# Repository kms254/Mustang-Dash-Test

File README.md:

# Mustang-Dash-Test

Firmware **and carrier hardware** for a **Riverdi EVE4 instrument cluster** —
a 7" centre panel with two 5" side panels, each on its **own dedicated SPI
peripheral**, driven by an **STM32H755**.

| Item      | Value |
|-----------|-------|
| Displays  | Centre: Riverdi **SM-RVT70HSBNWN00** — 7.0" **1024 × 600** IPS, **BT817** (EVE4), no touch. Sides: RVT50H. |
| MCU       | **STM32H755ZIT6** on the in-repo carrier (**Board3**, ordered from JLCPCB 2026-08). Bench mules: NUCLEO-H755ZI-Q (same die) and NUCLEO-F767ZI (proven three-panel rig). |
| Library   | [RudolphRiedel/FT800-FT813](https://github.com/RudolphRiedel/FT800-FT813) (EmbeddedVideoEngine) v5.0.10, branch `5.x`, vendored in [`libraries/`](libraries/) with multi-panel / per-panel-SPI-bus support |
| Profile   | `EVE_RVT70H` (1024×600, BT817, `EVE_GEN 4`) |

## Repo layout

| Path | What it is |
|---|---|
| [`MustangDash/`](MustangDash/) | The firmware sketch plus pure, host-tested headers (sim, serial, odometer, button, telltales) |
| [`kicad/board3/`](kicad/board3/) | The carrier board — schematic, routed PCB, footprint libraries. DRC/ERC 0 at `--severity-all`; reviewed pre-order by seven independent lenses |
| [`fab/`](fab/) | The JLCPCB package: gerbers/BOM/CPL plus [`ORDER.md`](fab/ORDER.md), the order-form contract every figure of which re-derives from the tree |
| [`tools/`](tools/) | The KiCad pipeline: `kicad_lcsc.py` (sourcing), `kicad_fab.py` (fab package), `kicad_verify.py` (the DRC gate), silk/routing/verification tooling |
| [`docs/hardware/`](docs/hardware/) | [Bring-up card](docs/hardware/board3-bringup-card.md) (print before the boards arrive) and the [as-built H755 pin map](docs/hardware/board3-h755-pin-map.md) |
| [`docs/solutions/`](docs/solutions/) + [`CONCEPTS.md`](CONCEPTS.md) | Documented learnings (YAML frontmatter: `module`, `tags`, `problem_type`) and the shared domain vocabulary |

## Wiring

Shared ground, panel logic on **3.3 V**, backlight on an external **5.0 V**
supply (a dev board's USB rail cannot feed three backlights).

**Each panel has its own SPI peripheral** — on Board3: centre SPI1
(PA5/6/7, CS PD8, PD PD11), left SPI2 (PB13/14/15, CS PD9, PD PD12), right
SPI4 (PE2/5/6, CS PE3, PD PD13) — plus per-panel CS and PD/RST. Panel timings
live in [`MustangDash/dash_panels.h`](MustangDash/dash_panels.h); per-target
pins in the sketch's board blocks and the
[pin map](docs/hardware/board3-h755-pin-map.md). `INT` is not wired — the
firmware polls.

**SPI is mode 0, MSB-first, ≤ 11 MHz during every panel's `EVE_init()`**, then
each bus rises once to the run clock. **Board3 runs 25 MHz on all three
panels**, walked and soaked 2026-08-21; the F767 bench ran 13.5 (where 27 MHz
hard-wedges the firmware rather than degrading gracefully). Two numbers, two
clock trees, both correct — because clock numbers come from failure, not
derivation, and **do not transfer across copper**: re-walk on each new board,
per the bring-up card. And the constant is only a *request* — the peripheral
rounds it down to a reachable rung, so ask the firmware what it actually got
(`diag` on the serial console prints the attained rate per panel) rather than
trusting the source.

## What the firmware does

A 2000 ms animated boot splash (ASTC assets embedded in the MCU image and
staged to RAM_G with per-asset readback checks) crossfades into the dash, which
renders TRACK and STREET screens procedurally at ~60 fps with custom EVE bitmap
fonts.

Data flows simulator → `DashState` channels → renderers; CAN decoders will fill
the same channels later. The serial protocol (115200, USB-CDC on Board3;
`ok`/`err` acks) overrides any channel; the odometer persists across power
cycles. A short press on the gesture button (BTN1 on Board3, the USER button on
the mules) toggles TRACK/STREET; a ≥1 s hold resets the trip. Telltales drive
eight LEDs through two AW9523B expanders on I2C2; the boot banner self-checks
the panels, the expanders, and the QSPI NOR's JEDEC ID.

## Build

See [`BUILD.md`](BUILD.md) for the environments and the flash budget.

```bash
./scripts/compile.sh                    # PlatformIO, default env nucleo_f767
./scripts/compile.sh board3             # the carrier (25 MHz crystal clock tree)
./scripts/compile.sh board3_mule        # same firmware on the NUCLEO-H755ZI-Q
wsl -- bash -lc "./tests/run-tests.sh"  # host invariant tests, no board needed
```

**H755 targets, one-time first connect:** the factory chip boots both cores and
the CM4 has no image — run `STM32_Programmer_CLI -c port=SWD -ob BCM4=0` once.
The mule env is SMPS-aware (flashing plain `board3` onto the -Q Nucleo hangs at
the VOSRDY wait); details and the session matrix are on the
[bring-up card](docs/hardware/board3-bringup-card.md).

The host tests pin what must not silently change: the `EVE_RVT70H` profile, the
control pins, the backlight sweep, the splash timeline, the dash
math/sim/serial/odometer logic, the font format, the flash-pack layout, the
button gestures and the telltale calibration.

## Configuration (already applied in the vendored library)

- **Profile** — `EVE_config.h` defines `EVE_RVT70H` near the top of the file,
  so it applies without `-D` flags. Note it is **not** `EVE_RiTFT70`, which is
  the 800×480 BT81x panel — picking that one initialises fine and renders
  garbage. See [the profile-selection
  learning](docs/solutions/best-practices/riverdi-rvt70h-vs-ritft70-eve-display-profile-selection.md).
- **Multi-panel** — the STM32 target header carries `EVE_MULTI_PANEL` and a
  per-panel descriptor (`EVE_panel_t`) with an optional per-panel `SPIClass*`
  bus; the sketch selects the active panel at runtime.
- An Arduino `library.properties` was added so the `src/` layout is picked up
  (upstream ships only a PlatformIO `library.json`).

## Troubleshooting

| Symptom | Likely cause |
|---|---|
| Board looks completely dead | Hold **BOOT** + tap **RESET** → a DFU device on USB proves MCU, power and the USB path with zero tools. Then walk the [bring-up card](docs/hardware/board3-bringup-card.md); on this bench a "dead board" has historically been a cable or connector, not silicon. |
| `EVE_init() did NOT return E_OK` | EVE never came out of reset — check PD/RST, the 3.3 V logic supply, and CS. |
| Init OK but `REG_ID = 0x00`/`0xFF` (not `0x7C`) | SPI link — MISO/MOSI swapped, wrong CS, or the clock too fast. `0x00` and `0xFF` distinguish a floating line from a stuck one. |
| Init OK and `REG_ID = 0x7C` but the panel stays dark | Backlight power or `REG_PWM_DUTY`. The panel is alive but unlit — it renders fine with no 5 V on BLVDD, just invisibly. |
| Init OK, backlight lit, image garbled or wrong geometry | Wrong display profile in `EVE_config.h`. |

More hard-won detail — FFC orientation, identifying the backlight end by
continuity, why instruments that answer confidently deserve suspicion — is in
[`docs/solutions/`](docs/solutions/), organised by category with searchable
frontmatter.

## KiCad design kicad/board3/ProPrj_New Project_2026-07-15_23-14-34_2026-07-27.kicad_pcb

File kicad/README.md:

# kicad/

The project's board designs.

Today that is **Board3**. It arrived here as an import from EasyEDA Pro for the
tooling evaluation in
[docs/plans/2026-07-27-001-chore-kicad-evaluation-plan.md](../docs/plans/2026-07-27-001-chore-kicad-evaluation-plan.md),
but **that evaluation is settled**: as of 2026-07-31 Kevin has moved off EasyEDA
entirely, so this directory is the design, not a copy of one.

| Top | Bottom |
| --- | --- |
|  |  |

These are generated, not drawn — `.kicad_pcb` is the truth. See
[Renders](#renders) for how they stay current.

Three rules govern everything in this directory:

- **This is the source of truth.** ~~EasyEDA stays authoritative; conversion is
  one-way.~~ Superseded 2026-07-31 — EasyEDA is no longer maintained, so there is
  no upstream to defer to and nothing to reconcile against. Edit the schematic and
  board here directly. The `EasyEDA/` directory stays in the repo as history; do
  not mirror changes into it, and do not treat a KiCad-only change as partial.
  The one-way rule still describes the *import*: nothing here was ever converted
  back, and `docs/solutions/integration-issues/easyeda-pro-to-kicad-migration-silent-data-loss.md`
  records six silent losses that make a re-import a bad idea now that this copy
  carries all the routing.
- **The design files are tracked on purpose.** `.kicad_pcb` and `.kicad_sch` are
  S-expression text, and `git diff` is the evaluation's verification mechanism for
  agent-driven writes. Keeping the board out of the repo would forfeit that.
- **The first commit of a converted board is the baseline.** It must contain
  converter output and nothing else. Every later measurement diffs against it.

Toolchain resolution for anything operating on these files is
[tools/kicad_env.py](../tools/kicad_env.py) — do not hardcode `kicad-cli` paths.

**Never pick a board by globbing for the newest `.kicad_pcb`.** Routing and
cascade experiments leave variant boards (`…-c0.kicad_pcb`, `…-it.kicad_pcb`)
sitting beside the real one, and being scratch they are *always* newer — so
newest-wins reliably selects the wrong file. This bit twice on 2026-07-28:
`kicad_render.py` rendered a leftover temp board, and `kicad_live_view.py` spent
a session watching one that was then deleted underneath it. Filter to files git
tracks (`git ls-files -- '*.kicad_pcb'`) and take the newest of those; untracked
neighbours are working scratch, not the design.

## Renders

`board3/renders/*.png` are committed so the board is visible in a diff, a PR, or
a browser without installing KiCad. They are **build output, not source** — the
board is the truth and these are regenerated from it:

```sh
python tools/kicad_render.py            # refresh all three views
python tools/kicad_render.py --check    # exit 2 if older than the board
```

A tracked pre-commit hook keeps them honest. Install it once per clone:

```sh
git config core.hooksPath .githooks
```

The hook is convenience, not enforcement — it is opt-in per clone, so it is
silently absent on a fresh clone or under `--no-verify`. CI is what actually
holds the line: `.github/workflows/kicad-renders.yml` fails any PR that changes
the board without refreshing the renders, and `kicad-parts.yml` runs the part
audit on every PR.

The hook only fires when a `.kicad_pcb` is actually staged — each refresh is
~360 KB of binary that lands in history permanently, so regenerating on every
commit would bloat the repo to show a picture that did not change. If rendering
fails (no KiCad on this machine) it warns and lets the commit through: refusing
to commit firmware because a PCB picture could not be drawn is the wrong trade.

Renders are 1200×750 on purpose. Enough to read placement and routing at a
glance; open the board if you need detail.

## Watching the board change live

To see the board *while* an agent edits it, without pcbnew in the way:

```sh
python tools/kicad_live_view.py                     # newest board under kicad/
python tools/kicad_live_view.py path/to/x.kicad_pcb --port 8010
```

It serves a local page that renders the file with
[KiCanvas](https://kicanvas.org/) and reloads on every save, keeping your zoom.
Pan/zoom, layer toggles and net highlight all work.

**3D is on the second tab**, built by `kicad-cli` in the background — but only
while that tab is open, since a build costs real CPU and nobody would see it.
Two modes, because the cost difference is an order of magnitude:

| mode | what it is | board3 |
|---|---|---|
| **snapshot** (default) | `pcb render` PNG, six camera presets | **~3 s**, 0.1 MB |
| **model** | `export glb`, orbit in the browser | **~29 s**, 13.5 MB |
| **model + copper** | as above with tracks/zones/silk as geometry | **~47 s**, 31 MB |

So 3D follows an agent at roughly one frame per edit, not live — the header
always says how far behind it is (`3D showing rev 4, board at rev 7`) rather
than quietly showing you a stale board. Snapshot is the default because 3 s is
fast enough to actually watch work happen; switch to model when you want to
orbit something. There is no cheap middle: a components-free GLB builds in 1.2 s
but is a bare board, which is no use for checking a footprint.

Model mode opens **top-down on the top face** (model-viewer's own default is
nearly edge-on, which on a board this thin is a sliver). That framing is applied
once, so an orbit you set up afterwards survives every rebuild.

3D is built from the *same validated bytes* the 2D tab is showing, written to a
temp copy — so the two tabs can never disagree and a build can never catch a
half-written save. That relocation would normally drop every 3D model, since
footprints reference `${KIPRJMOD}/EASYEDA_MODELS/…` and KIPRJMOD follows the
file; the builder passes `-D KIPRJMOD=<board dir>` to put them back. Worth
knowing because the failure is silent — without it you get a bare green board
and no error.

**Why not just open pcbnew.** The editor takes a `.lck` on the board and holds
its own in-memory copy, so an agent's write and your session become two
authorities on one file — whoever saves last wins, silently. This viewer only
ever reads. That is also why it is a *viewer*: it is safe to leave open all day
precisely because it cannot write, so it does not replace the GUI for editing,
and KTD12 still holds (Update PCB from Schematic is Kevin, in the GUI, after a
restart).

Two things worth knowing:

- **A save is not atomic from the reader's side.** Every re-read is validated
  (starts with `(kicad_pcb`, parens balance outside strings) before it is
  published, so a file caught mid-write never reaches the screen — the viewer
  holds the last good revision and turns its status dot amber. Verified by
  truncating a board under a running viewer: revision held, bytes served
  unchanged.
- **KiCanvas predates KiCad 10 and skips tokens it does not know**, warning to
  the browser console. On board3 that is 344 warnings and zero errors, all of
  them non-geometry policy fields (`tenting`, `covering`, `plugging`, `capping`,
  `filling`, `duplicate_pad_numbers_are_jumpers`, dimension `units`). Copper,
  zones, footprints and silk all render. It is a preview, not an authority —
  DRC and the fab package remain the check that matters.

The bundle is cached to `tools/vendor/kicanvas.js` on first run (gitignored);
`--refresh-viewer` re-fetches it.

## Adding a part

**Every part placed on a board here must be an LCSC part, carrying supplier
metadata and a 3D model.** Not a convention — a build dependency. `kicad_fab.py`
builds the JLCPCB BOM by reading the schematic's supplier fields, so a part added
without them does not produce a warning, it produces a BOM that is quietly
missing a component.

Add parts with [tools/kicad_lcsc.py](../tools/kicad_lcsc.py), never by dragging a
generic symbol out of the stock KiCad libraries:

```sh
python tools/kicad_lcsc.py add C116592   # symbol + footprint + STEP/WRL + metadata
python tools/kicad_lcsc.py check         # audit; exits non-zero on any gap
python tools/kicad_lcsc.py models        # fetch any 3D model the board references but lacks
```

`add` drives the JLCImport plugin and then rewrites the imported symbol's fields
into Board3's vocabulary. That rewrite is the whole point: JLCImport writes the
LCSC code to a property named `LCSC`, and this project reads it from
`Supplier Part`. Import without remapping and the part looks sourced in the
schematic editor while being invisible to the BOM.

`LCSC Part Name` is **not** the part number despite its name — it holds
descriptive text. The C-number goes in `Supplier Part`.

Run `check` before generating fab output. It audits the **board**, not the
library — the board is what gets fabricated, and each placed footprint carries
its own copy of the model reference, so an instance placed before a library fix
can be wrong while the library looks perfect. It fails on any of:

- a placed part **not mapped to LCSC** (missing `Supplier Part`, or absent from
  the schematic entirely)
- a placed footprint with **no 3D model reference at all**
- a model reference whose **file is missing from disk**
- a schematic symbol with no LCSC code, placed or not

Footprints that legitimately have no body — fiducials, free pads, mounting
holes, test points — are exempt via the `BODILESS` table in the tool, and every
exemption is **printed on every run**. An exemption you cannot see is one you
cannot audit, and that table is the only path by which a real part could pass
unnoticed. Board3 currently exempts 8: three fiducials, four free pads (MP1-MP4) and H2, the Tag-Connect land pattern -- a cable presses pogo pins onto bare copper, so nothing is fitted and there is no part to source.

3D models live in `board3/EASYEDA_MODELS/` and **are tracked** (~53 MB, ~9.5 MB
in history). They are regenerable from the schematic's LCSC codes via
`kicad_lcsc.py models`, but they are committed anyway so a fresh clone renders
and exports 3D offline, and so the geometry stays pinned to this board revision
rather than to whatever EasyEDA serves later.

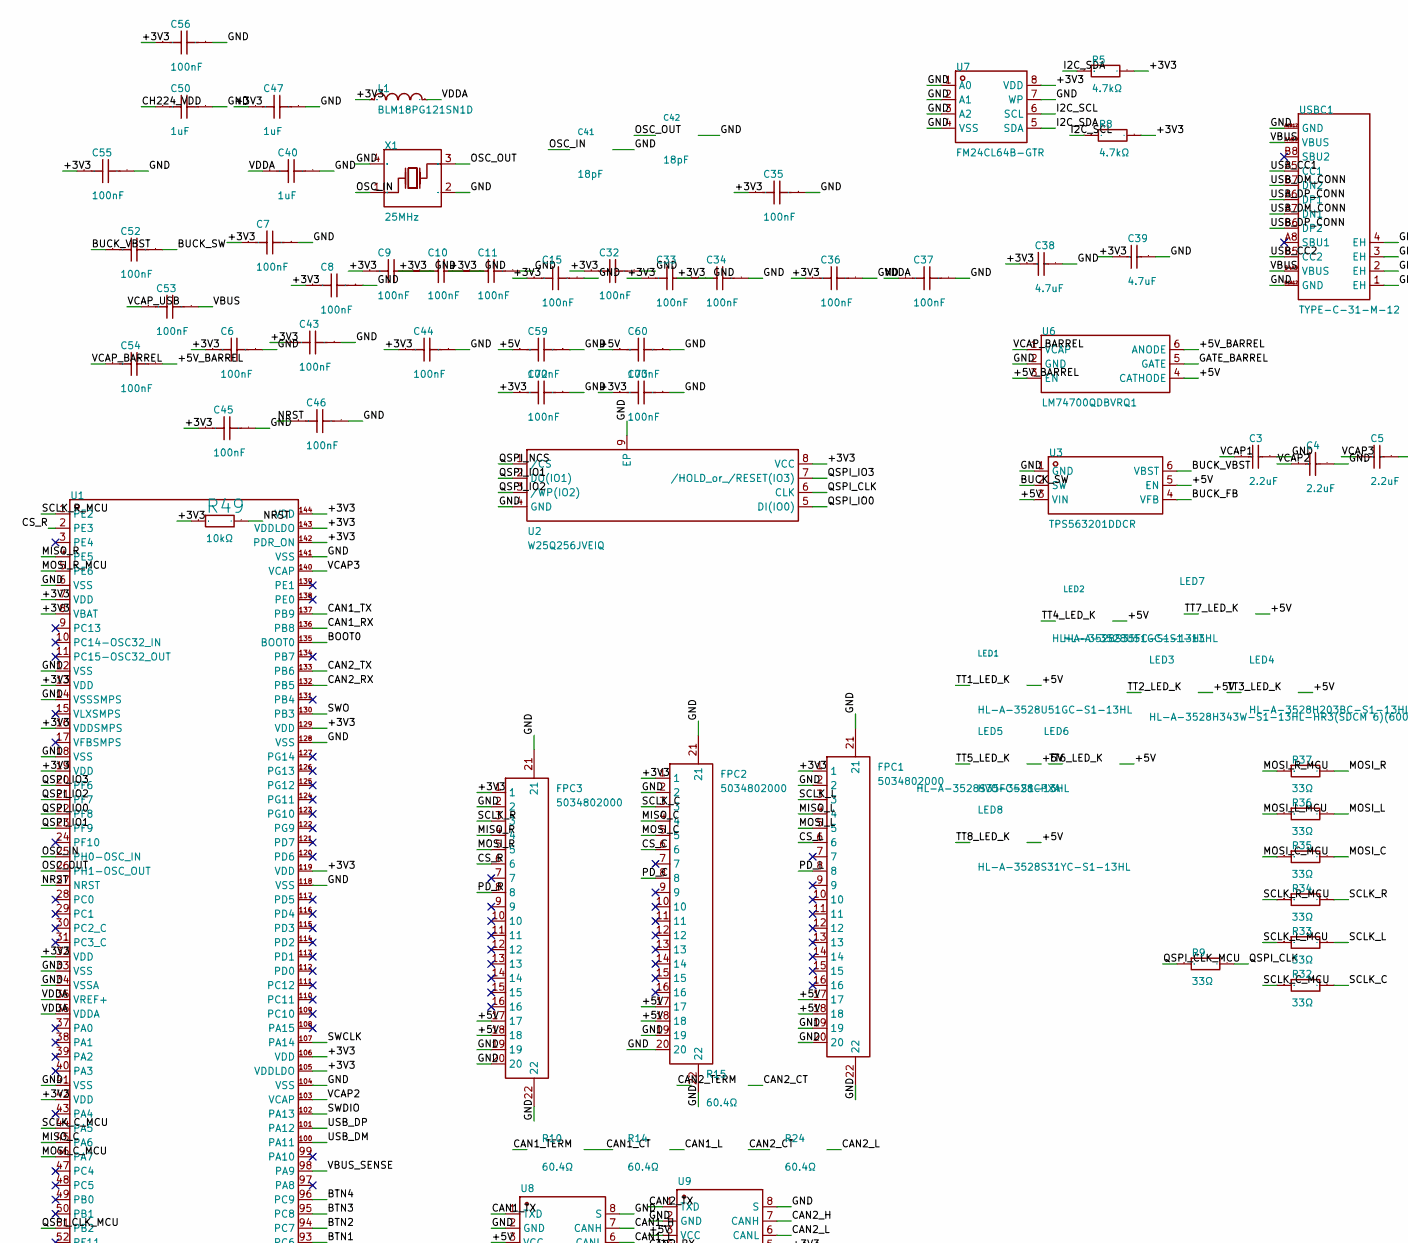
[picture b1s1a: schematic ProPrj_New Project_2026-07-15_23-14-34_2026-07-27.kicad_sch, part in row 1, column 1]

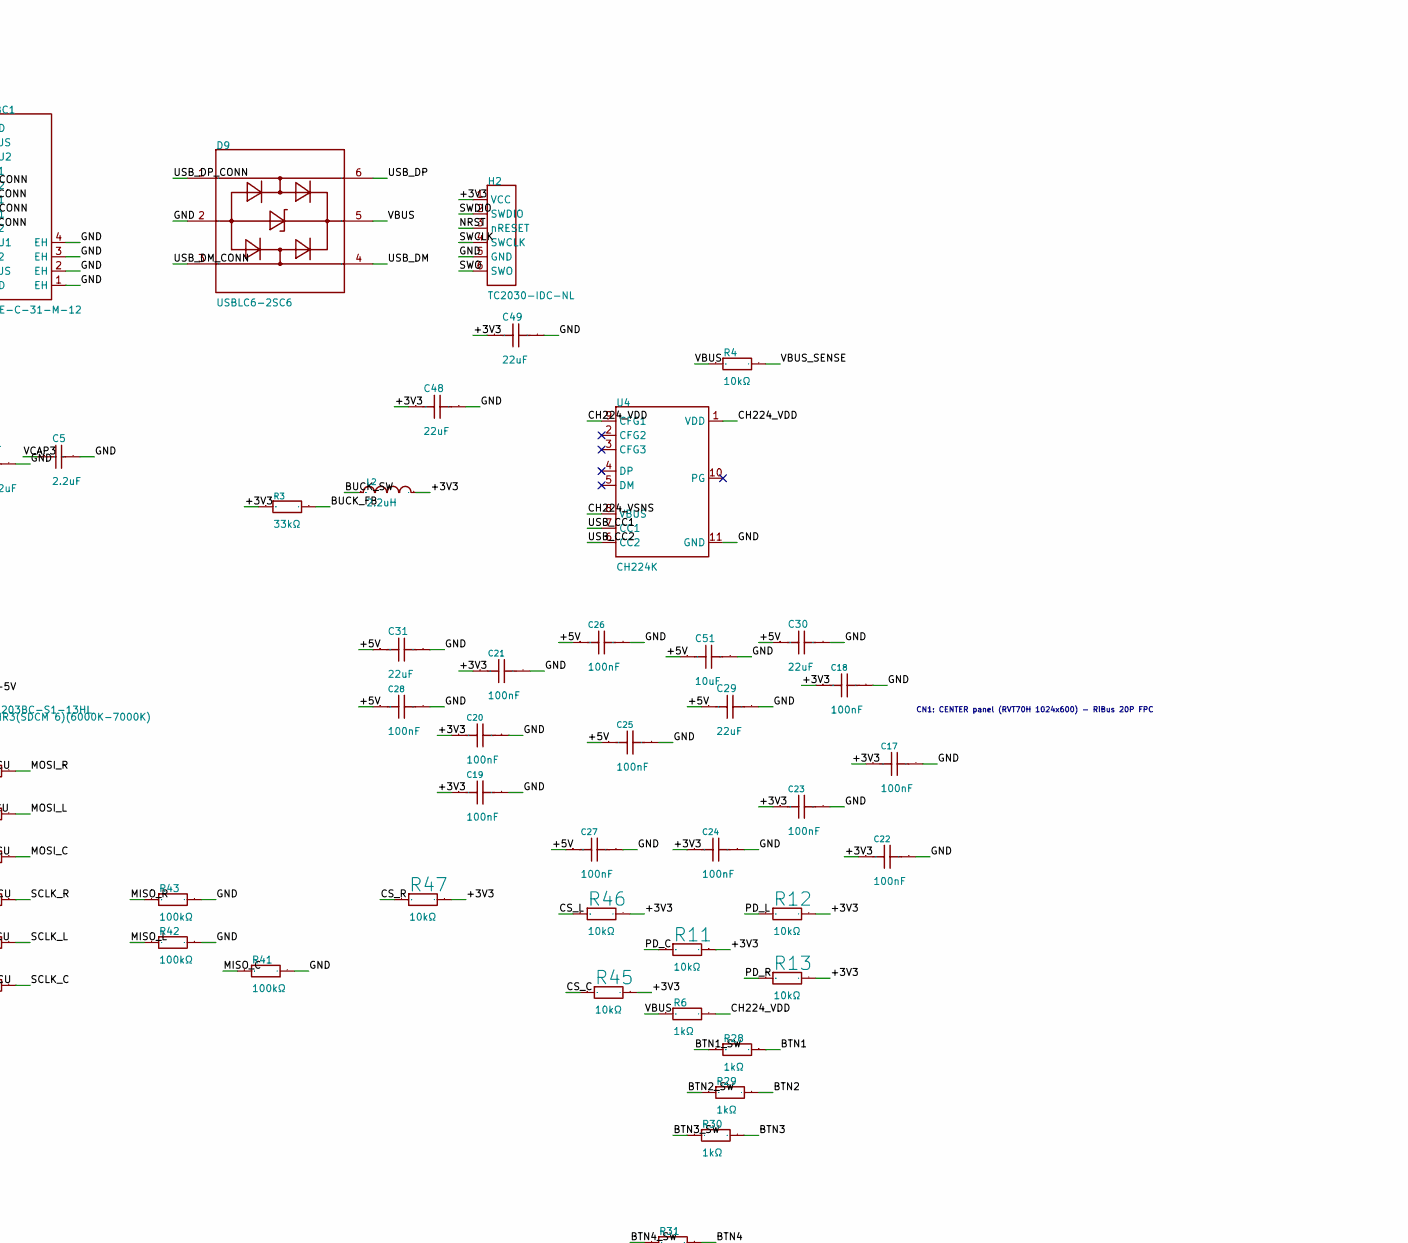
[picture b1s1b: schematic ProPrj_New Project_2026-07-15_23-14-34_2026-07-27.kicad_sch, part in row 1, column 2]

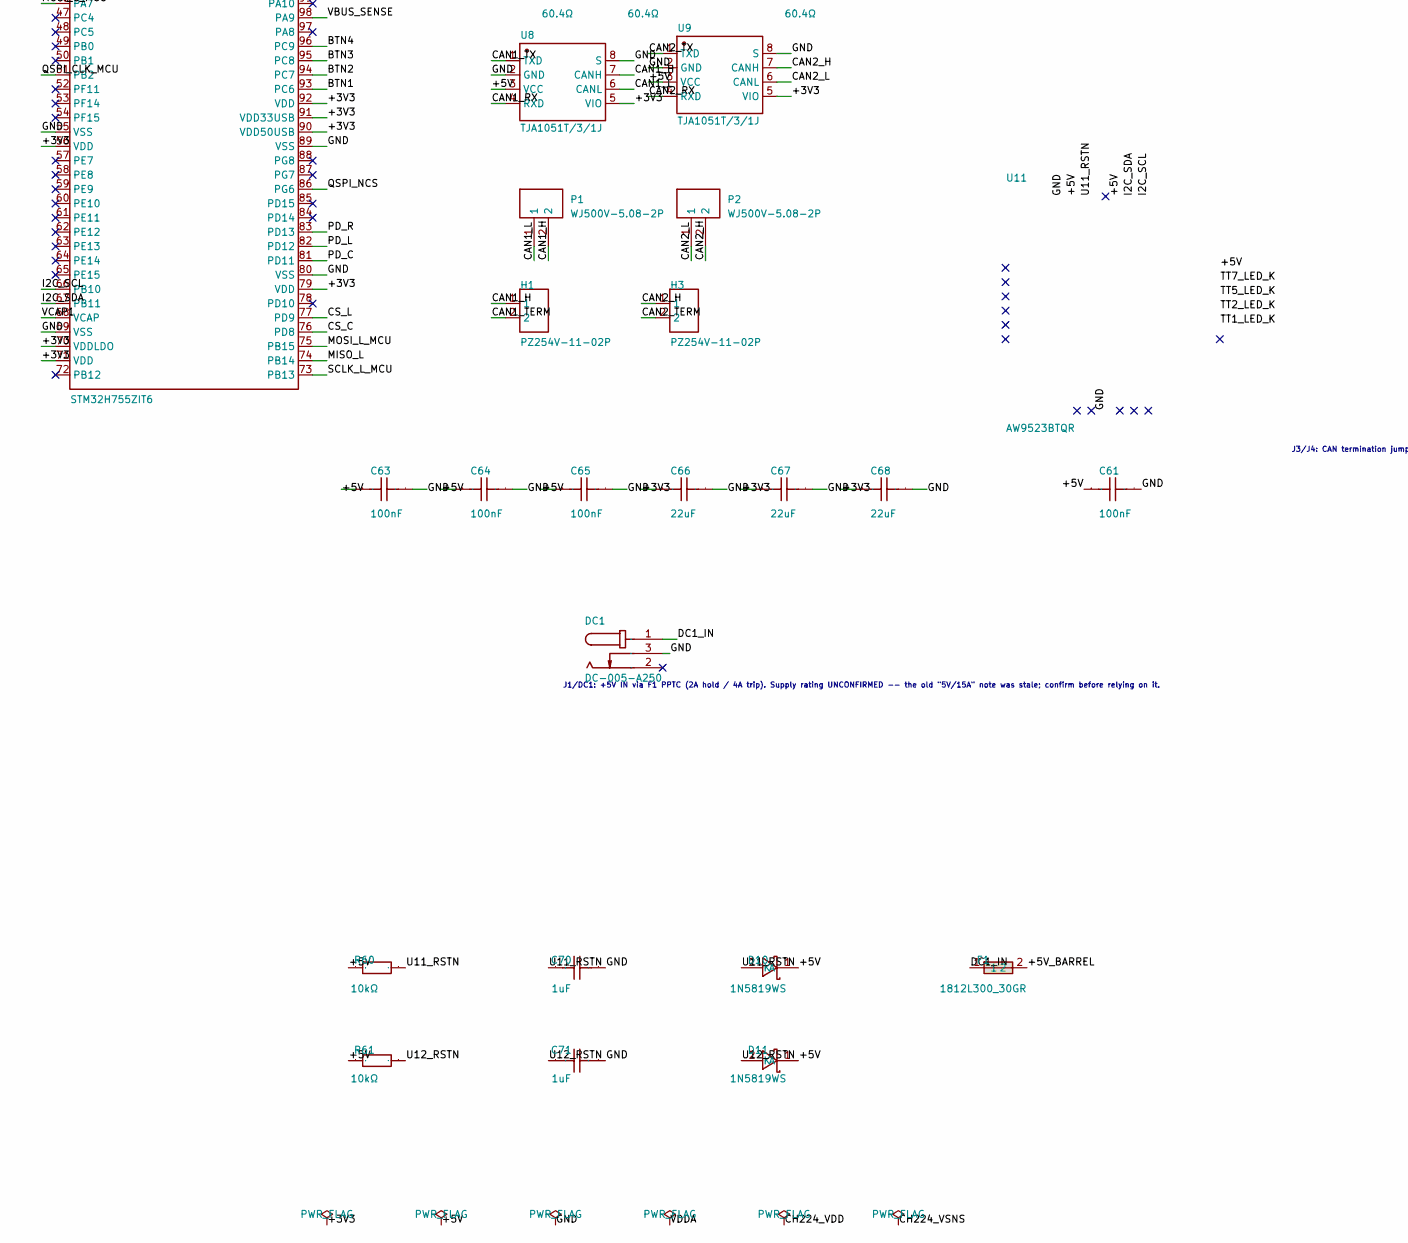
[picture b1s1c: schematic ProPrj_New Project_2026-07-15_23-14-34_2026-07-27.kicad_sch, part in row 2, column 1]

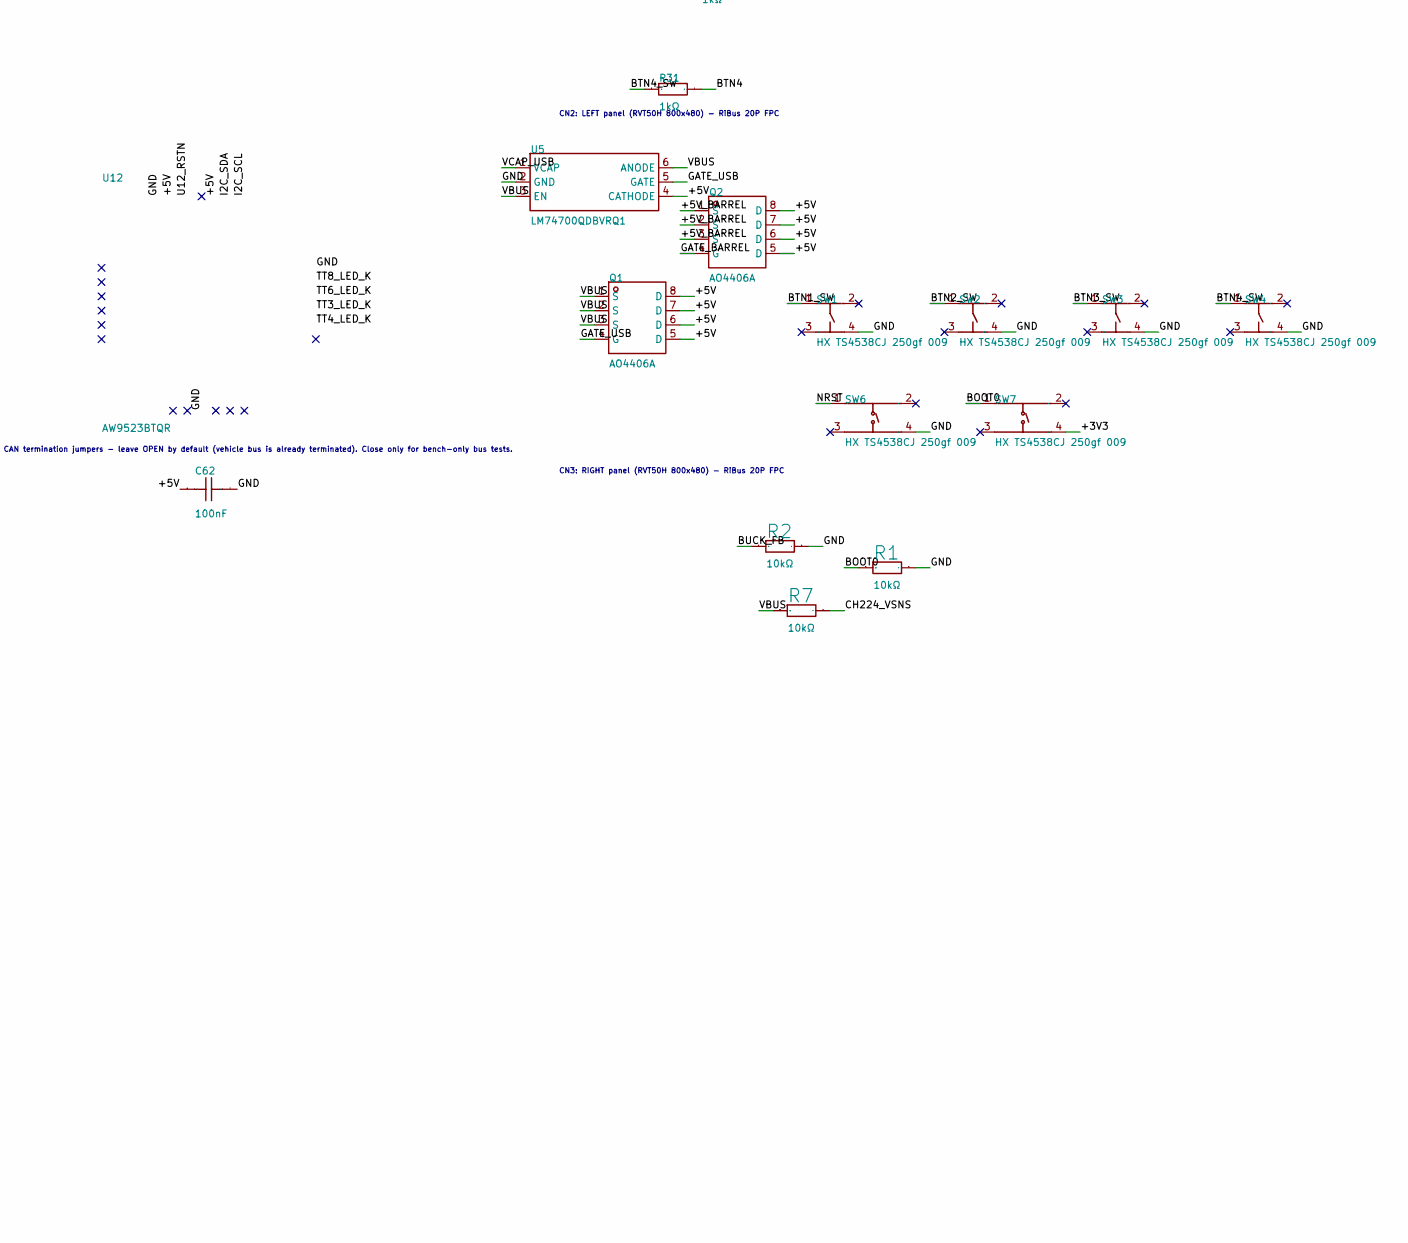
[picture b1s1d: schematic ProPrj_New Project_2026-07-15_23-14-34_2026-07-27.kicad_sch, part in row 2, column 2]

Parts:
C3, C4, C5: 2.2uF; C0603; Manufacturer Part CL10A225KO8NNNC; JLCPCB Part Class Basic Part
C6, C17, C18, C19, C20, C21, C22, C23, C24, C25, C26, C27, C28, C35, C37, C43, C44, C45, C46, C52, C53, C54, C55, C56, C59, C60, C61, C62, C63, C64, C65, C72, C73: 100nF; C0603; Tolerance ±10%; Voltage Rating 50V; Manufacturer Part CC0603KRX7R9BB104; LCSC Part Name 100nF ±10% 50V
C7, C8, C9, C10, C11, C15, C32, C33, C34, C36: 100nF; C0603; Manufacturer Part CC0603KRX7R9BB104; JLCPCB Part Class Basic Part
C29, C30, C31, C66, C68: 22uF; C0805; Tolerance ±10%; Voltage Rating 25V; Manufacturer Part CL21A226MAQNNNE; LCSC Part Name 22uF ±20% 25V
C38, C39: 4.7uF; C0805; Manufacturer Part CL21A475KAQNNNE; JLCPCB Part Class Basic Part
C40, C70, C71: 1uF; C0603; Manufacturer Part CL10A105KB8NNNC; JLCPCB Part Class Basic Part
C41, C42: 18pF; C0603; Manufacturer Part CL10C180JB8NNNC; LCSC Part Name 18pF ±5% 50V
C47, C50: 1uF; C0603; Tolerance ±10%; Voltage Rating 50V; Manufacturer Part CL10A105KB8NNNC; LCSC Part Name 1uF ±10% 50V
C48, C49: 22uF; C0805; Tolerance ±20%; Voltage Rating 25V; Manufacturer Part CL21A226MAQNNNE; LCSC Part Name 22uF ±20% 25V
C51: 10uF; C0805; Tolerance ±10%; Voltage Rating 25V; Manufacturer Part CL21A106KAYNNNE; LCSC Part Name 10uF ±10% 25V
C67: 22uF; C0805; Tolerance ±10%; Voltage Rating 25V; Manufacturer Part CL21A226MAQNNNE; LCSC Part Name 10uF ±10% 10V
D9: USBLC6-2SC6; SOT-23-6_L2.9-W1.6-P0.95-LS2.8-BL; Clamping Voltage 17V; Voltage - Breakdown 6V; Manufacturer Part USBLC6-2SC6; LCSC Part Name 单向ESD
D10, D11: 1N5819WS; Manufacturer Part 1N5819WS; JLCPCB Part Class Basic Part
DC1: DC-005-A250; DC-IN-TH_DC-005-2; Manufacturer Part DC-005-A250; LCSC Part Name DC-005-5.5*2.5
F1: 1812L300_30GR; Manufacturer Part 1812L300/30GR; JLCPCB Part Class Extended Part
FPC1, FPC2, FPC3: 5034802000; FPC-SMD_5034802000; Current Rating (Max) 500mA; Rated Voltage (Max) 50V; Manufacturer Part 5034802000; LCSC Part Name 翻盖式 双侧触点/上下接 P数:20P 间距:0.5mm
H1, H3: PZ254V-11-02P; HDR-TH_2P-P2.54-V-M; Current Rating 3A; Voltage Rating (Max) 250V; Manufacturer Part PZ254V-11-02P; LCSC Part Name 1x2P 间距:2.54mm 方针 直插
H2: TC2030-IDC-NL; Tag-Connect_TC2030-IDC-NL_2x03_P1.27mm_Vertical
L1: BLM18PG121SN1D; L0603; Manufacturer Part BLM18PG121SN1D; JLCPCB Part Class Basic Part
L2: 2.2uH; IND-SMD_L4.0-W4.0_FNR40XXS; Current Rating 3.2A; Tolerance ±20%; Manufacturer Part FNR4030S2R2MT; LCSC Part Name 2.2uH ±20% 5.8A
LED1, LED2: HL-A-3528U51GC-S1-13HL; Voltage - Forward(Vf) 3.4V; Manufacturer Part HL-A-3528U51GC-S1-13HL; LCSC Part Name HL-A-3528U51GC-S1-13HL
LED3: HL-A-3528H343W-S1-13HL-HR3(SDCM 6)(6000K-7000K); HL-A-3528H343W-S1-13HL-HR3_SDCM_amp_lt_6_6000K-7000K; Voltage - Forward(Vf) 3.2V; Manufacturer Part HL-A-3528H343W-S1-13HL-HR3(SDCM 6)(6000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; LCSC Part Name HL-A-3528H343W-S1-13HL-HR3_SDCM_amp_lt_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
LED4: HL-A-3528H203BC-S1-13HL; Voltage - Forward(Vf) 3.4V; Manufacturer Part HL-A-3528H203BC-S1-13HL; LCSC Part Name HL-A-3528H203BC-S1-13HL
LED5: HVO-3528CPXA; Voltage - Forward(Vf) 2.2V; Manufacturer Part HVO-3528CPXA; LCSC Part Name HVO-3528CPXA
LED6, LED7: HL-A-3528S35FC-S1-13HL; Voltage - Forward(Vf) 2.4V; Manufacturer Part HL-A-3528S35FC-S1-13HL; LCSC Part Name HL-A-3528S35FC-S1-13HL
LED8: HL-A-3528S31YC-S1-13HL; Voltage - Forward(Vf) 2.4V; Manufacturer Part HL-A-3528S31YC-S1-13HL; LCSC Part Name HL-A-3528S31YC-S1-13HL
P1, P2: WJ500V-5.08-2P; CONN-TH_2P-P5.00_WJ500V-5.08-2P; Current Rating 18A; Voltage Rating (Max) 250V; Manufacturer Part WJ500V-5.08-2P; LCSC Part Name 1x2P 5.08mm 直插 排数:1 每排P数:2
Q1, Q2: AO4406A; SOP-8_L5.0-W3.8-P1.27-LS6.0-BL; Manufacturer Part AO4406A; LCSC Part Name 1个N沟道 耐压:30V 电流:12A
R1, R2, R4, R7, R11, R12, R13, R45, R46, R47, R49: 10kΩ; R0603; Tolerance ±1%; Voltage-Supply(Max) 75V; Manufacturer Part 0603WAF1002T5E; LCSC Part Name 厚膜电阻 10kΩ ±1% 100mW
R3: 33kΩ; R0603; Tolerance ±1%; Voltage-Supply(Max) 75V; Manufacturer Part 0603WAF3302T5E; LCSC Part Name 33kΩ ±1% 100mW 厚膜电阻
R5, R8: 4.7kΩ; R0603; Tolerance ±1%; Voltage-Supply(Max) 75V; Manufacturer Part 0603WAF4701T5E; LCSC Part Name 4.7kΩ ±1% 100mW 厚膜电阻
R6, R28, R29, R30, R31: 1kΩ; R0603; Tolerance ±1%; Voltage-Supply(Max) 75V; Manufacturer Part 0603WAF1001T5E; LCSC Part Name 1kΩ ±1% 100mW 厚膜电阻
R9, R32, R33, R34, R35, R36, R37: 33Ω; R0603; Tolerance ±1%; Voltage-Supply(Max) 75V; Manufacturer Part 0603WAF330JT5E; LCSC Part Name 33Ω ±1% 100mW 厚膜电阻
R10, R14, R15, R24: 60.4Ω; ERJP06F60R4V; Tolerance ±1%; Voltage-Supply(Max) 75V; Manufacturer Part ERJP06F60R4V; LCSC Part Name ERJP06F60R4V
R41, R42, R43: 100kΩ; R0603; Tolerance ±1%; Voltage-Supply(Max) 75V; Manufacturer Part 0603WAF1003T5E; LCSC Part Name 100kΩ ±1% 100mW 厚膜电阻
R60, R61: 10kΩ; R0603; Manufacturer Part 0603WAF1002T5E; JLCPCB Part Class Basic Part
SW1, SW2, SW3, SW4, SW6, SW7: HX TS4538CJ 250gf 009; SW-TH_4P-L4.5-W4.5-P3.00-LS5.0; Manufacturer Part HX TS4538CJ 250gf 009; JLCPCB Part Class Extended Part
U1: STM32H755ZIT6; LQFP-144_L20.0-W20.0-P0.50-LS22.0-BL; Manufacturer Part STM32H755ZIT6; JLCPCB Part Class Extended Part
U2: W25Q256JVEIQ; WSON-8_L8.0-W6.0-P1.27-TL-EP; Manufacturer Part W25Q256JVEIQ; JLCPCB Part Class Extended Part
U3: TPS563201DDCR; SOT-23-6_L2.9-W1.6-P0.95-LS2.8-BR; Manufacturer Part TPS563201DDCR; JLCPCB Part Class Extended Part
U4: CH224K; ESSOP-10_L4.9-W3.9-P1.0-LS6.0-TL-EP; Output Voltage 5V；20V；15V；12V；9V; Voltage - Supply 4V~30V; Manufacturer Part CH224K; LCSC Part Name USBPD等多快充协议受电芯片CH224
U5, U6: LM74700QDBVRQ1; SOT-23-6_L2.9-W1.6-P0.95-LS2.8-BL; Manufacturer Part LM74700QDBVRQ1; LCSC Part Name 低IQ电池反向保护理想二极管控制器
U7: FM24CL64B-GTR; SOIC-8_L4.9-W3.9-P1.27-LS6.0-BL; Voltage - Supply 2.7V~3.65V; Manufacturer Part FM24CL64B-GTR; LCSC Part Name FM24CL64B-GTR
U8, U9: TJA1051T/3/1J; SOIC-8_L4.9-W3.9-P1.27-LS6.0-BL; Supply Voltage 4.5V~5.5V; Manufacturer Part TJA1051T/3/1J; LCSC Part Name TJA1051T/3/1J
U11, U12: AW9523BTQR; Manufacturer Part AW9523BTQR; LCSC Part Name AW9523BTQR
USBC1: TYPE-C-31-M-12; USB-C_SMD-TYPE-C-31-M-12_1; Current Rating-Power 5A; Voltage Rating 20V; Manufacturer Part TYPE-C-31-M-12; LCSC Part Name Type-C 母 卧贴
X1: 25MHz; CRYSTAL-SMD_4P-L3.2-W2.5-BL; Manufacturer Part X322525MOB4SI; JLCPCB Part Class Basic Part

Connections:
/+3V3: C6.1, C7.1, C8.1, C9.1, C10.1, C11.1, C15.1, C17.1, C18.1, C19.1, C20.1, C21.1, C22.1, C23.1, C24.1, C32.1, C33.1, C34.1, C35.1, C36.1, C38.1, C39.1, C43.1, C44.1, C45.1, C47.1, C48.1, C49.1, C55.1, C56.1, C66.1, C67.1, C68.1, C72.1, C73.1, FPC1.1, FPC2.1, FPC3.1, H2.1 (VCC), L1.1, L2.2, R3.1, R5.2, R8.2, R11.2, R12.2, R13.2, R45.2, R46.2, R47.2, R49.1, SW7.4 (D), U1.7 (VDD), U1.8 (VBAT), U1.13 (VDD), U1.16 (VDDSMPS), U1.19 (VDD), U1.32 (VDD), U1.42 (VDD), U1.56 (VDD), U1.70 (VDDLDO), U1.71 (VDD), U1.79 (VDD), U1.90 (VDD50USB), U1.91 (VDD33USB), U1.92 (VDD), U1.105 (VDDLDO), U1.106 (VDD), U1.119 (VDD), U1.129 (VDD), U1.142 (PDR_ON), U1.143 (VDDLDO), U1.144 (VDD), U2.8 (VCC), U7.8 (VDD), U8.5 (VIO), U9.5 (VIO)
/+5V: C25.1, C26.1, C27.1, C28.1, C29.1, C30.1, C31.1, C51.1, C59.1, C60.1, C61.1, C62.1, C63.1, C64.1, C65.1, D10.1 (K), D11.1 (K), FPC1.17, FPC1.18, FPC2.17, FPC2.18, FPC3.17, FPC3.18, LED1.2 (A), LED2.2 (A), LED3.2 (A), LED4.2 (+), LED5.2 (A), LED6.2 (A), LED7.2 (A), LED8.2 (+), Q1.5 (D), Q1.6 (D), Q1.7 (D), Q1.8 (D), Q2.5 (D), Q2.6 (D), Q2.7 (D), Q2.8 (D), R60.1, R61.1, U3.3 (VIN), U3.5 (EN), U5.4 (CATHODE), U6.4 (CATHODE), U8.3 (VCC), U9.3 (VCC), U11.18 (AD0), U11.21 (VCC), U11.24 (AD1), U12.21 (VCC), U12.24 (AD1)
/+5V_BARREL: C54.2, F1.2, Q2.1 (S), Q2.2 (S), Q2.3 (S), U6.3 (EN), U6.6 (ANODE)
/BOOT0: R1.1, SW7.1 (A), U1.135 (BOOT0)
/BTN1: R28.2, U1.93 (PC6)
/BTN1_SW: R28.1, SW1.1
/BTN2: R29.2, U1.94 (PC7)
/BTN2_SW: R29.1, SW2.1
/BTN3: R30.2, U1.95 (PC8)
/BTN3_SW: R30.1, SW3.1
/BTN4: R31.2, U1.96 (PC9)
/BTN4_SW: R31.1, SW4.1
/BUCK_FB: R2.1, R3.2, U3.4 (VFB)
/BUCK_SW: C52.2, L2.1, U3.2 (SW)
/BUCK_VBST: C52.1, U3.6 (VBST)
/CAN1_CT: R10.2, R14.1
/CAN1_H: H1.1, P1.2, U8.7 (CANH)
/CAN1_L: P1.1, R14.2, U8.6 (CANL)
/CAN1_RX: U1.136 (PB8), U8.4 (RXD)
/CAN1_TERM: H1.2, R10.1
/CAN1_TX: U1.137 (PB9), U8.1 (TXD)
/CAN2_CT: R15.2, R24.1
/CAN2_H: H3.1, P2.2, U9.7 (CANH)
/CAN2_L: P2.1, R24.2, U9.6 (CANL)
/CAN2_RX: U1.132 (PB5), U9.4 (RXD)
/CAN2_TERM: H3.2, R15.1
/CAN2_TX: U1.133 (PB6), U9.1 (TXD)
/CH224_VDD: C50.1, R6.2, U4.1 (VDD), U4.9 (CFG1)
/CH224_VSNS: R7.2, U4.8 (VBUS)
/CS_C: FPC2.6, R45.1, U1.76 (PD8)
/CS_L: FPC1.6, R46.1, U1.77 (PD9)
/CS_R: FPC3.6, R47.1, U1.2 (PE3)
/DC1_IN: DC1.1, F1.1
/GATE_BARREL: Q2.4 (G), U6.5 (GATE)
/GATE_USB: Q1.4 (G), U5.5 (GATE)
/GND: C3.2, C4.2, C5.2, C6.2, C7.2, C8.2, C9.2, C10.2, C11.2, C15.2, C17.2, C18.2, C19.2, C20.2, C21.2, C22.2, C23.2, C24.2, C25.2, C26.2, C27.2, C28.2, C29.2, C30.2, C31.2, C32.2, C33.2, C34.2, C35.2, C36.2, C37.2, C38.2, C39.2, C40.2, C41.2, C42.2, C43.2, C44.2, C45.2, C46.2, C47.2, C48.2, C49.2, C50.2, C51.2, C55.2, C56.2, C59.2, C60.2, C61.2, C62.2, C63.2, C64.2, C65.2, C66.2, C67.2, C68.2, C70.2, C71.2, C72.2, C73.2, D9.2, DC1.3, FPC1.2, FPC1.19, FPC1.20, FPC1.21, FPC1.22, FPC2.2, FPC2.19, FPC2.20, FPC2.21, FPC2.22, FPC3.2, FPC3.19, FPC3.20, FPC3.21, FPC3.22, H2.5 (GND), R1.2, R2.2, R41.2, R42.2, R43.2, SW1.4, SW2.4, SW3.4, SW4.4, SW6.4 (D), U1.6 (VSS), U1.12 (VSS), U1.14 (VSSSMPS), U1.18 (VSS), U1.33 (VSS), U1.34 (VSSA), U1.41 (VSS), U1.55 (VSS), U1.69 (VSS), U1.80 (VSS), U1.89 (VSS), U1.104 (VSS), U1.118 (VSS), U1.128 (VSS), U1.141 (VSS), U2.4 (GND), U2.9 (EP), U3.1 (GND), U4.11 (GND), U5.2 (GND), U6.2 (GND), U7.1 (A0), U7.2 (A1), U7.3 (A2), U7.4 (VSS), U7.7 (WP), U8.2 (GND), U8.8 (S), U9.2 (GND), U9.8 (S), U11.9 (GND), U11.25 (GND), U12.9 (GND), U12.18 (AD0), U12.25 (GND), USBC1.1 (EH), USBC1.2 (EH), USBC1.3 (EH), USBC1.4 (EH), USBC1.A1B12 (GND), USBC1.B1A12 (GND), X1.2 (GND), X1.4 (GND); also elsewhere on the board
/I2C_SCL: R8.1, U1.66 (PB10), U7.6 (SCL), U11.19 (SCL), U12.19 (SCL)
/I2C_SDA: R5.1, U1.67 (PB11), U7.5 (SDA), U11.20 (SDA), U12.20 (SDA)
/MISO_C: FPC2.4, R41.1, U1.45 (PA6)
/MISO_L: FPC1.4, R42.1, U1.74 (PB14)
/MISO_R: FPC3.4, R43.1, U1.4 (PE5)
/MOSI_C: FPC2.5, R35.2
/MOSI_C_MCU: R35.1, U1.46 (PA7)
/MOSI_L: FPC1.5, R36.2
/MOSI_L_MCU: R36.1, U1.75 (PB15)
/MOSI_R: FPC3.5, R37.2
/MOSI_R_MCU: R37.1, U1.5 (PE6)
/NRST: C46.1, H2.3 (nRESET), R49.2, SW6.1 (A), U1.27 (NRST)
/OSC_IN: C41.1, U1.25 (PH0-OSC_IN), X1.1 (OSC1)
/OSC_OUT: C42.1, U1.26 (PH1-OSC_OUT), X1.3 (OSC2)
/PD_C: FPC2.8, R11.1, U1.81 (PD11)
/PD_L: FPC1.8, R12.1, U1.82 (PD12)
/PD_R: FPC3.8, R13.1, U1.83 (PD13)
/QSPI_CLK: R9.2, U2.6 (CLK)
/QSPI_CLK_MCU: R9.1, U1.51 (PB2)
/QSPI_IO0: U1.22 (PF8), U2.5 (DI(IO0))
/QSPI_IO1: U1.23 (PF9), U2.2 (DO(IO1))
/QSPI_IO2: U1.21 (PF7), U2.3 (/WP(IO2))
/QSPI_IO3: U1.20 (PF6), U2.7 (/HOLD_or_/RESET(IO3))
/QSPI_NCS: U1.86 (PG6), U2.1 (/CS)
/SCLK_C: FPC2.3, R32.2
/SCLK_C_MCU: R32.1, U1.44 (PA5)
/SCLK_L: FPC1.3, R33.2
/SCLK_L_MCU: R33.1, U1.73 (PB13)
/SCLK_R: FPC3.3, R34.2
/SCLK_R_MCU: R34.1, U1.1 (PE2)
/SWCLK: H2.4 (SWCLK), U1.107 (PA14)
/SWDIO: H2.2 (SWDIO), U1.102 (PA13)
/SWO: H2.6 (SWO), U1.130 (PB3)
/TT1_LED_K: LED1.1 (C), U11.14 (P1_4)
/TT2_LED_K: LED3.1 (C), U11.15 (P1_5)
/TT3_LED_K: LED4.1 (-), U12.15 (P1_5)
/TT4_LED_K: LED2.1 (C), U12.14 (P1_4)
/TT5_LED_K: LED5.1 (K), U11.16 (P1_6)
/TT6_LED_K: LED6.1 (K), U12.16 (P1_6)
/TT7_LED_K: LED7.1 (K), U11.17 (P1_7)
/TT8_LED_K: LED8.1 (-), U12.17 (P1_7)
/U11_RSTN: C70.1, D10.2 (A), R60.2, U11.23 (RSTN)
/U12_RSTN: C71.1, D11.2 (A), R61.2, U12.23 (RSTN)
/USB_CC1: U4.7 (CC1), USBC1.A5 (CC1)
/USB_CC2: U4.6 (CC2), USBC1.B5 (CC2)
/USB_DM: D9.4, U1.100 (PA11)
/USB_DM_CONN: D9.3, USBC1.A7 (DN1), USBC1.B7 (DN2)
/USB_DP: D9.6, U1.101 (PA12)
/USB_DP_CONN: D9.1, USBC1.A6 (DP1), USBC1.B6 (DP2)
/VBUS: C53.2, D9.5, Q1.1 (S), Q1.2 (S), Q1.3 (S), R4.1, R6.1, R7.1, U5.3 (EN), U5.6 (ANODE), USBC1.A4B9 (VBUS), USBC1.B4A9 (VBUS)
/VBUS_SENSE: R4.2, U1.98 (PA9)
/VCAP1: C3.1, U1.68 (VCAP)
/VCAP2: C4.1, U1.103 (VCAP)
/VCAP3: C5.1, U1.140 (VCAP)
/VCAP_BARREL: C54.1, U6.1 (VCAP)
/VCAP_USB: C53.1, U5.1 (VCAP)
/VDDA: C37.1, C40.1, L1.2, U1.35 (VREF+), U1.36 (VDDA)

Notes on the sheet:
J1/DC1: +5V IN via F1 PPTC (2A hold / 4A trip). Supply rating UNCONFIRMED -- the old "5V/15A" note was stale; confirm before relying on it.
CN2: LEFT panel (RVT50H 800x480) - RiBus 20P FPC
CN3: RIGHT panel (RVT50H 800x480) - RiBus 20P FPC
CN1: CENTER panel (RVT70H 1024x600) - RiBus 20P FPC
J3/J4: CAN termination jumpers - leave OPEN by default (vehicle bus is already terminated). Close only for bench-only bus tests.

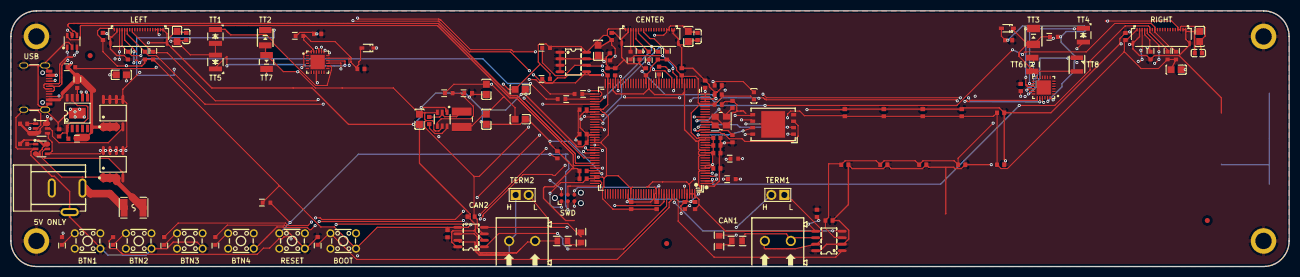
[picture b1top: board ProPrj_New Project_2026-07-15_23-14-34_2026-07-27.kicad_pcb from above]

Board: 4 copper layers, 250.0 x 50.0 mm, 150 parts (0 on the bottom side), 93 nets.

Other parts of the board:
FID1, FID2, FID3: Fiducial_1mm_Mask2mm
MP1: Pad_e672
MP2: Pad_e675
MP3: Pad_e673
MP4: Pad_e674

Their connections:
/GND: MP1.1, MP2.1, MP3.1, MP4.1; also elsewhere on the board

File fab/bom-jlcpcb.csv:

Comment,Designator,Footprint,LCSC Part #
2.2uF,"C3,C4,C5",C0603,C23630
100nF,"C6,C7,C8,C9,C10,C11,C15,C17,C18,C19,C20,C21,C22,C23,C24,C25,C26,C27,C28,C32,C33,C34,C35,C36,C37,C43,C44,C45,C46,C52,C53,C54,C55,C56,C59,C60,C61,C62,C63,C64,C65,C72,C73",C0603,C14663
22uF,"C29,C30,C31,C48,C49,C66,C67,C68",C0805,C45783
4.7uF,"C38,C39",C0805,C1779
1uF,"C40,C47,C50,C70,C71",C0603,C15849
18pF,"C41,C42",C0603,C1647
10uF,C51,C0805,C15850
USBLC6-2SC6,D9,SOT-23-6_L2.9-W1.6-P0.95-LS2.8-BL,C7519
1N5819WS,"D10,D11",1N5819WS,C191023
DC-005-A250,DC1,DC-IN-TH_DC-005-2,C720558
1812L300_30GR,F1,1812L300_30GR,C48985875
5034802000,"FPC1,FPC2,FPC3",FPC-SMD_5034802000,C234192
PZ254V-11-02P,"H1,H3",HDR-TH_2P-P2.54-V-M,C492401
BLM18PG121SN1D,L1,L0603,C14709
2.2uH,L2,IND-SMD_L4.0-W4.0_FNR40XXS,C167869
HL-A-3528U51GC-S1-13HL,"LED1,LED2",HL-A-3528U51GC-S1-13HL,C516142
HL-A-3528H343W-S1-13HL-HR3(SDCM 6)(6000K-7000K),LED3,HL-A-3528H343W-S1-13HL-HR3_SDCM_amp_lt_6_6000K-7000K,C516299
HL-A-3528H203BC-S1-13HL,LED4,HL-A-3528H203BC-S1-13HL,C516143
HVO-3528CPXA,LED5,HVO-3528CPXA,C5246349
HL-A-3528S35FC-S1-13HL,"LED6,LED7",HL-A-3528S35FC-S1-13HL,C516141
HL-A-3528S31YC-S1-13HL,LED8,HL-A-3528S31YC-S1-13HL,C516140
WJ500V-5.08-2P,"P1,P2",CONN-TH_2P-P5.00_WJ500V-5.08-2P,C8465
AO4406A,"Q1,Q2",SOP-8_L5.0-W3.8-P1.27-LS6.0-BL,C2944312
10k,"R1,R2,R4,R7,R11,R12,R13,R45,R46,R47,R49,R60,R61",R0603,C25804
33k,R3,R0603,C4216
4.7k,"R5,R8",R0603,C23162
1k,"R6,R28,R29,R30,R31",R0603,C21190
33,"R9,R32,R33,R34,R35,R36,R37",R0603,C23140
60.4,"R10,R14,R15,R24",ERJP06F60R4V,C3959530
100k,"R41,R42,R43",R0603,C25803
HX TS4538CJ 250gf 009,"SW1,SW2,SW3,SW4,SW6,SW7",SW-TH_4P-L4.5-W4.5-P3.00-LS5.0,C5340169
STM32H755ZIT6,U1,LQFP-144_L20.0-W20.0-P0.50-LS22.0-BL,C730212
W25Q256JVEIQ,U2,WSON-8_L8.0-W6.0-P1.27-TL-EP,C97522
TPS563201DDCR,U3,SOT-23-6_L2.9-W1.6-P0.95-LS2.8-BR,C116592
CH224K,U4,ESSOP-10_L4.9-W3.9-P1.0-LS6.0-TL-EP,C970725
LM74700QDBVRQ1,"U5,U6",SOT-23-6_L2.9-W1.6-P0.95-LS2.8-BL,C2941042
FM24CL64B-GTR,U7,SOIC-8_L4.9-W3.9-P1.27-LS6.0-BL,C9829
TJA1051T/3/1J,"U8,U9",SOIC-8_L4.9-W3.9-P1.27-LS6.0-BL,C38695
AW9523BTQR,"U11,U12",AW9523BTQR,C148077
TYPE-C-31-M-12,USBC1,USB-C_SMD-TYPE-C-31-M-12_1,C165948
25MHz,X1,CRYSTAL-SMD_4P-L3.2-W2.5-BL,C9006
